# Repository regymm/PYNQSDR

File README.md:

## PYNQSDR

### 🚀　**We're launching! Follow the updates on [Crowd Supply](https://www.crowdsupply.com/xtal-hart-tech/pynqsdr-hat)!**　🚀

PYNQ-Z1 + AD936X SDR platform and more. Openwifi & PlutoSDR capable. 

[KiCad files](./kicad) **|** [Design & future plan](Design.md) **|** [Talk on FOSDEM 2022](https://fosdem.org/2022/schedule/event/openwifipynqz1/) [Slides](doc/openwifi_pynqz1.pdf) **|** [Blog TBD] **|** [Quick start](Quickstart.md) **|** [EBAZSDR TBD]

**Boards are now for sale! Visit my store at [regymm's toy shop](https://regymm.github.io/regymm-toy-shop)!**

This project demonstrated that AD936X chip can combine with low-cost ZYNQ FPGA development boards, especially PYNQ-Z1, and run openwifi without problem. This can potentially become an extremely low-cost openwifi platform. And with extensions removed, you still have a PYNQ capable of any other serious ZYNQ projects. 

Going beyond PYNQ-Z1, this extension board can also combine with other hardware by easy 2-layer conversion board and provide even lower-cost platforms. 

#### Gallery

V1.1 board that works: 

Openwifi running on PYNQSDR: 

Board anatomy: 

#### Credits

Openwifi: https://github.com/open-sdr/openwifi

PlutoSDR: https://github.com/analogdevicesinc/plutosdr-fw

RF frontend PCB design based on https://github.com/kangyuzhe666/ZYNQ7010-7020_AD9363

Many online discussion groups also gave me a lot of help. 

#### License

GPLv3 for all board files. CC BY-SA for blog articles, documents, photos and the logo. Code are coming from different projects and should remain their original licenses.

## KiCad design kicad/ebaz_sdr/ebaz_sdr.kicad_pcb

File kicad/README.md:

#### PYNQSDR KiCad hardware

pynqsdr: main board, converted from Altium so expect small problems. KiCad nighty required. [Schematics PDF](./pynqsdr.pdf)

br1: HDMI and PMOD direct-connect bridge. 

br2: PMOD bridge with LVDS driver DS90LV047A or SN65LVDS047A. Need 2 of this in initial release and current release(v1.1). 

br3: HDMI bridge with LVDS receiver DS90LVDS048A and PMOD direct-connect. 

br4: HDMI bridge with 4x LVDS to CML translator SN65CML100. Need 2 of this in inital release. 

br5: HDMI bridge with crossing and PMOD direct-connect bridge. 

**v1.1** release requirement: two HDMI direct-connect (br1), two DS90LVDS047A (br2)

**Initial** release requirement: two 4x SN65CML100 (br4), two DS90LVDS047A (br2)

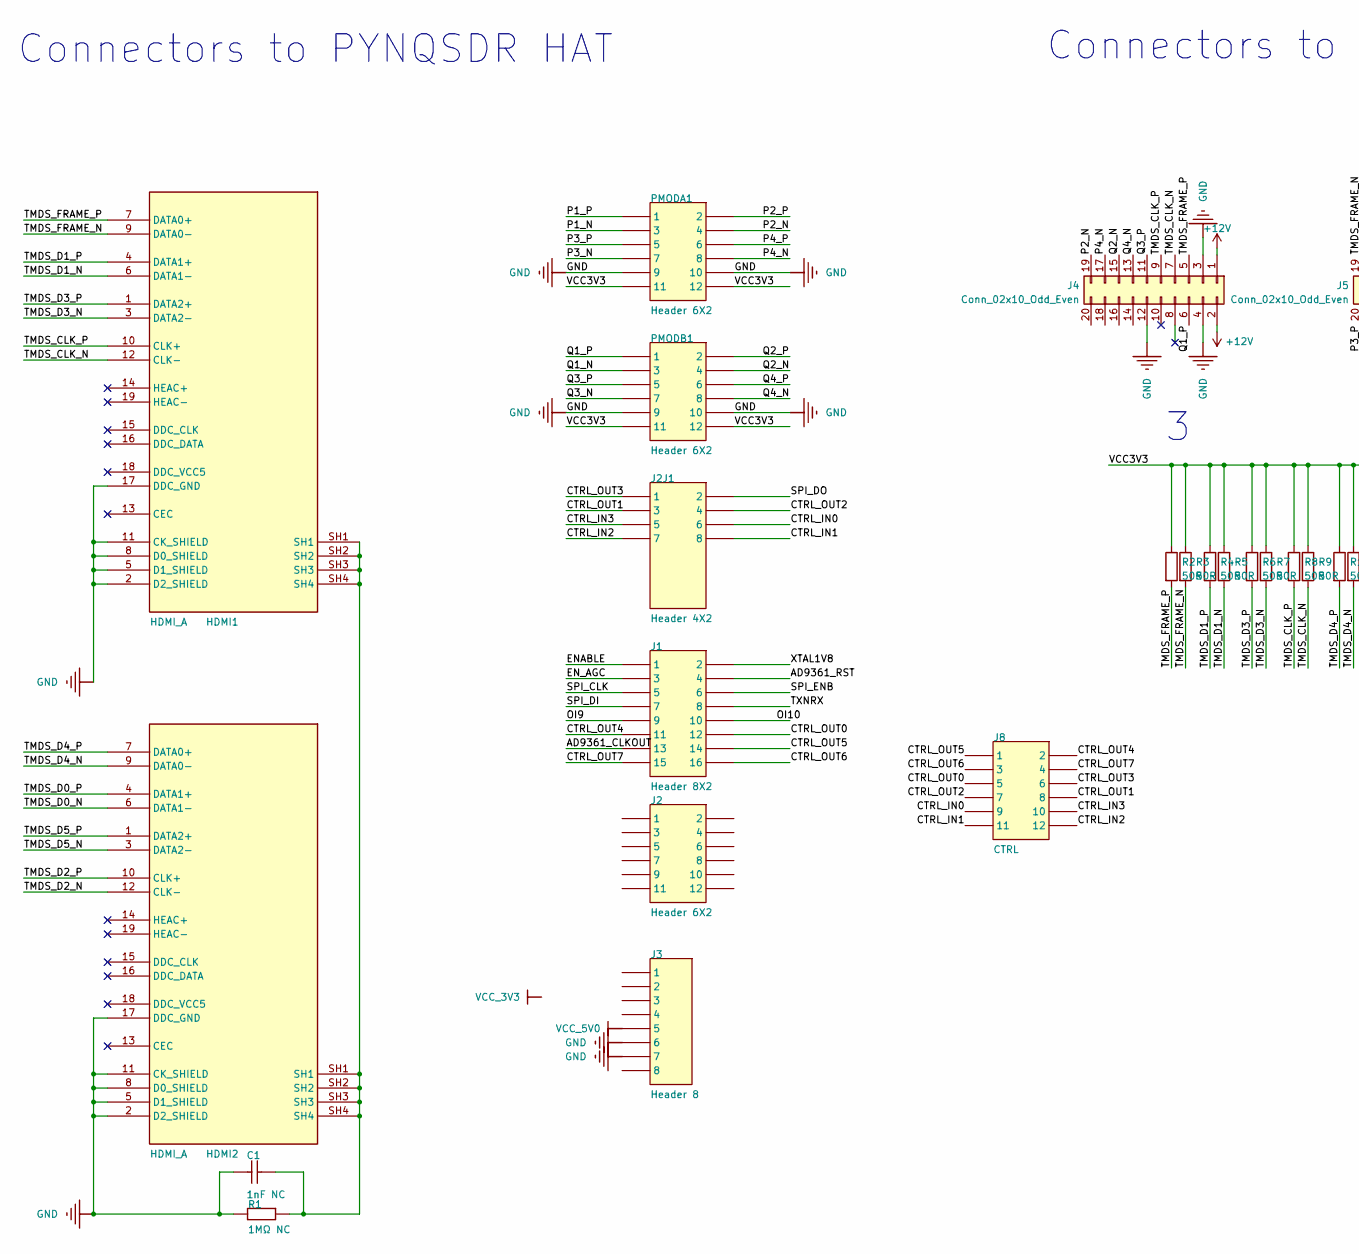
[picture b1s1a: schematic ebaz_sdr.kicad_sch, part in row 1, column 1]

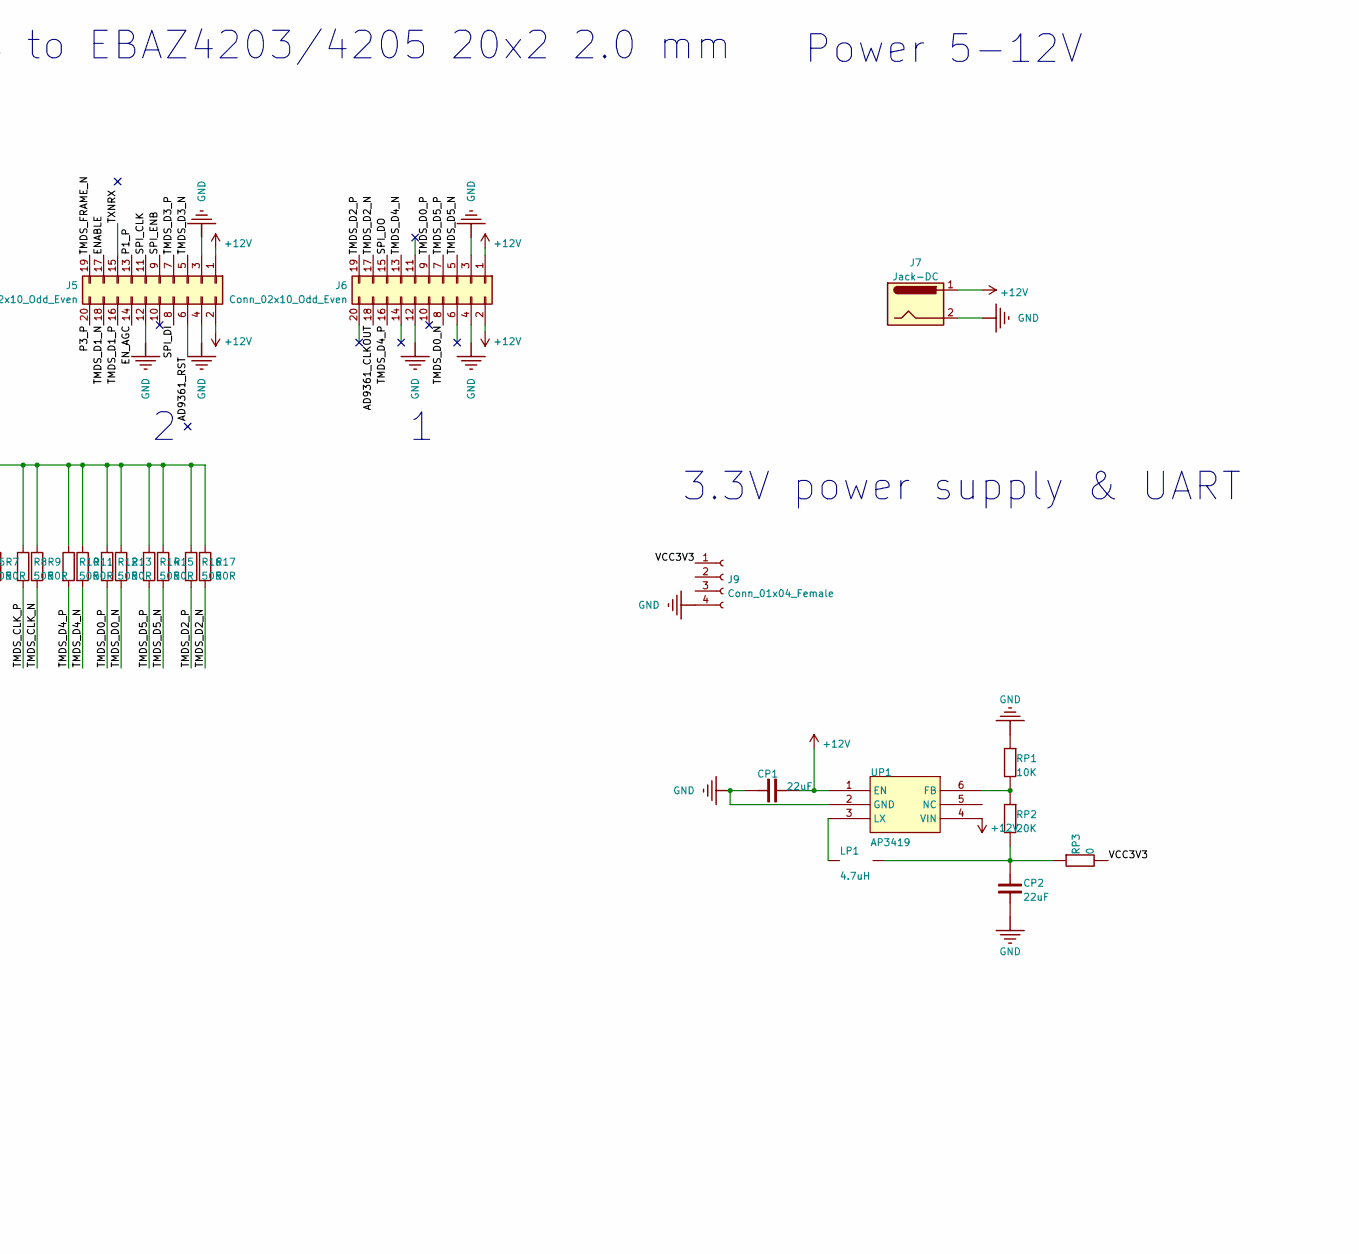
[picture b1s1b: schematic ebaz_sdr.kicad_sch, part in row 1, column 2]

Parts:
C1: 1nF NC; R_0603_1608Metric_Pad0.98x0.95mm_HandSolder
CP1, CP2: 22uF; LC-0805_C
HDMI1, HDMI2: HDMI_A
J1: Header 8X2; HDR2X8
J2: Header 6X2; HDR2X6
J2J1: Header 4X2; HDR2X8
J3: Header 8; HDR1X8
J4, J5, J6: Conn_02x10_Odd_Even; PinSocket_2x10_P2.00mm_Horizontal
J7: Jack-DC; BarrelJack_Wuerth_6941xx301002
J8: CTRL; HDR2X6
J9: Conn_01x04_Female; PinHeader_1x04_P2.54mm_Vertical
LP1: 4.7uH; L1008
PMODA1: Header 6X2; HDR2X6
PMODB1: Header 6X2; HDR2X6
R1: 1MΩ NC; R_0603_1608Metric_Pad0.98x0.95mm_HandSolder
R2, R3, R4, R5, R6, R7, R8, R9, R10, R11, R12, R13, R14, R15, R16, R17: 50R; R_0402_1005Metric_Pad0.72x0.64mm_HandSolder
RP1: 10K; LC-0402_R
RP2: 20K; LC-0402_R
RP3: 0; LC-0402_R
UP1: AP3419

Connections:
+12V: CP1.2, J4.1, J4.2, J5.1, J5.2, J6.1, J6.2, J7.1, UP1.1 (EN), UP1.4 (VIN)
/AD9361_CLKOUT: J1.13, J6.18
/AD9361_RST: J1.4, J5.6
/CTRL_IN0: J2J1.6, J8.9
/CTRL_IN1: J2J1.8, J8.11
/CTRL_IN2: J2J1.7, J8.12
/CTRL_IN3: J2J1.5, J8.10
/CTRL_OUT0: J1.12, J8.5
/CTRL_OUT1: J2J1.3, J8.8
/CTRL_OUT2: J2J1.4, J8.7
/CTRL_OUT3: J2J1.1, J8.6
/CTRL_OUT4: J1.11, J8.2
/CTRL_OUT5: J1.14, J8.1
/CTRL_OUT6: J1.16, J8.3
/CTRL_OUT7: J1.15, J8.4
/ENABLE: J1.1, J5.17
/EN_AGC: J1.3, J5.14
/OI9: J1.9
/OI10: J1.10
/P1_N: PMODA1.3
/P1_P: J5.13, PMODA1.1
/P2_N: J4.19, PMODA1.4
/P2_P: PMODA1.2
/P3_N: PMODA1.7
/P3_P: J5.20, PMODA1.5
/P4_N: J4.17, PMODA1.8
/P4_P: PMODA1.6
/Q1_N: PMODB1.3
/Q1_P: J4.6, PMODB1.1
/Q2_N: J4.15, PMODB1.4
/Q2_P: PMODB1.2
/Q3_N: PMODB1.7
/Q3_P: J4.11, PMODB1.5
/Q4_N: J4.13, PMODB1.8
/Q4_P: PMODB1.6
/SPI_CLK: J1.5, J5.11
/SPI_DI: J1.7, J5.8
/SPI_DO: J2J1.2, J6.15
/SPI_ENB: J1.6, J5.9
/TMDS_CLK_N: HDMI1.12 (CLK-), J4.7, R9.2
/TMDS_CLK_P: HDMI1.10 (CLK+), J4.9, R8.2
/TMDS_D0_N: HDMI2.6 (DATA1-), J6.8, R13.2
/TMDS_D0_P: HDMI2.4 (DATA1+), J6.9, R12.2
/TMDS_D1_N: HDMI1.6 (DATA1-), J5.18, R5.2
/TMDS_D1_P: HDMI1.4 (DATA1+), J5.16, R4.2
/TMDS_D2_N: HDMI2.12 (CLK-), J6.17, R17.2
/TMDS_D2_P: HDMI2.10 (CLK+), J6.19, R16.2
/TMDS_D3_N: HDMI1.3 (DATA2-), J5.5, R7.2
/TMDS_D3_P: HDMI1.1 (DATA2+), J5.7, R6.2
/TMDS_D4_N: HDMI2.9 (DATA0-), J6.13, R11.2
/TMDS_D4_P: HDMI2.7 (DATA0+), J6.16, R10.2
/TMDS_D5_N: HDMI2.3 (DATA2-), J6.5, R15.2
/TMDS_D5_P: HDMI2.1 (DATA2+), J6.7, R14.2
/TMDS_FRAME_N: HDMI1.9 (DATA0-), J5.19, R3.2
/TMDS_FRAME_P: HDMI1.7 (DATA0+), J4.5, R2.2
/TXNRX: J1.8, J5.15
/VCC3V3: J9.1, PMODA1.11, PMODA1.12, PMODB1.11, PMODB1.12, R2.1, R3.1, R4.1, R5.1, R6.1, R7.1, R8.1, R9.1, R10.1, R11.1, R12.1, R13.1, R14.1, R15.1, R16.1, R17.1, RP3.1
/XTAL1V8: J1.2
GND: C1.2, CP1.1, CP2.1, HDMI1.2 (D2_SHIELD), HDMI1.5 (D1_SHIELD), HDMI1.8 (D0_SHIELD), HDMI1.11 (CK_SHIELD), HDMI1.17 (DDC_GND), HDMI2.2 (D2_SHIELD), HDMI2.5 (D1_SHIELD), HDMI2.8 (D0_SHIELD), HDMI2.11 (CK_SHIELD), HDMI2.17 (DDC_GND), J3.6, J3.7, J4.3, J4.4, J4.12, J5.3, J5.4, J5.12, J6.3, J6.4, J6.12, J7.2, J9.4, PMODA1.9, PMODA1.10, PMODB1.9, PMODB1.10, R1.2, RP1.2, UP1.2 (GND)
unnamed: C1.1, HDMI1.SH1, HDMI1.SH2, HDMI1.SH3, HDMI1.SH4, HDMI2.SH1, HDMI2.SH2, HDMI2.SH3, HDMI2.SH4, R1.1
unnamed: CP2.2, LP1.2, RP2.1, RP3.2
unnamed: LP1.1, UP1.3 (LX)
unnamed: RP1.1, RP2.2, UP1.6 (FB)
VCC_5V0: J3.5

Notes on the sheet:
Power 5-12V
Connectors to EBAZ4203/4205 20x2 2.0 mm
Connectors to PYNQSDR HAT
3.3V power supply & UART
3 2 1

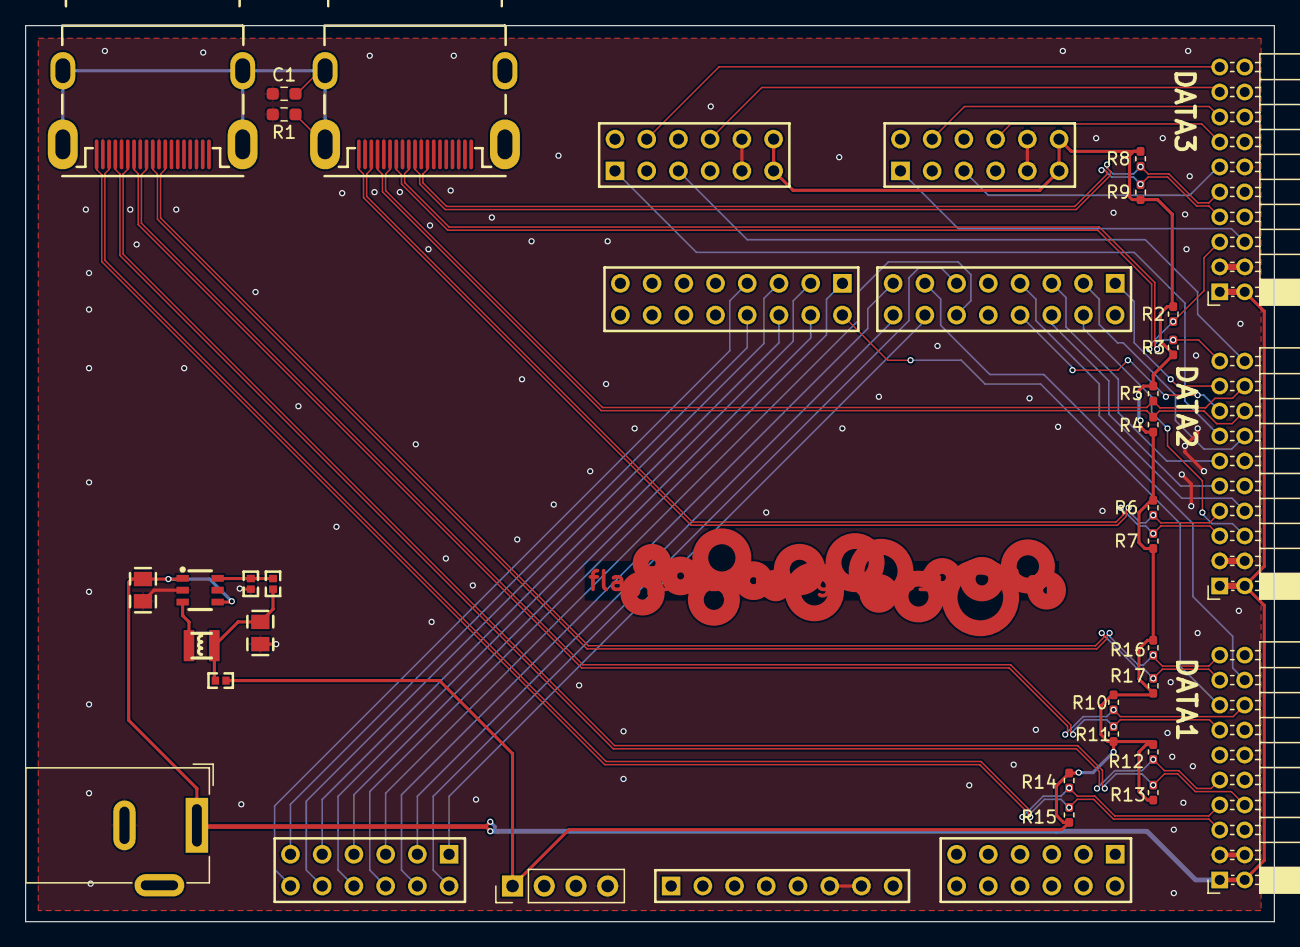
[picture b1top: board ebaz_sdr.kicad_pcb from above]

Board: 2 copper layers, 100.0 x 71.8 mm, 39 parts (0 on the bottom side), 52 nets.
